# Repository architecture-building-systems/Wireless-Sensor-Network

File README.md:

# Wireless Sensor Network

## Introduction
This repository contains all files needed to reproduce the Wireless Sensor Network (WSN) used for the Data-Driven Building Retrofit Research of the [A/S Chair](http://www.systems.arch.ethz.ch/). 
The WSN is intended to be deployed in residential buildings to collect sensor data for building model calibration. The microcontroller boards are based on the Arduino framework. For wireless communication, XBee radio modules are used.

See the [Wiki](https://github.com/architecture-building-systems/Wireless-Sensor-Network/wiki) for documentation, instructions, and other resources.

## Structure of the WSN
  
Sensor-Kit: (from left to right) two sensor nodes, gateway and router node

The WSN has a modular structure. The main components are the following:
* Gateway
* Router Node
* Sensor Node

On the sensor node, the sensor readings are performed and the data is relayed over router nodes to the gateway using the XBee network. The gateway forwards the data over cellular network to a web server, where the data is stored in a MySQL database. It is also possible to use a sensor node as data logger without any radio communication.

### Sensor Node
Sensor nodes consist of two parts: the main module and the sensor module. The sensor module interfaces the actual sensor(s). It reads out the sensor reading and transmits the result via the serial bus in a unified format to the main module. The main module interfaces the sensor module, radio transceiver, and the battery. It forwards the readings from the sensor module to the gateway. Both, the main module and the sensor module, can be programmed using the Arduino IDE.

#### Main Module
The main module is the same on all sensor nodes. It entails the following:
* Microcontroller (ATmega328p)
* Real-time clock (DS3231)
* Battery (2000mAh LiPo)
* SD-card socket
* XBee radio module (XB24CZ7WIT-004)
* Slide switch and LEDs for debugging
* Power jack for external power
* Connectors to sensor module

The tasks of the main module are:
* Scheduling (RTC or interrupt from sensor module)
* Interfacing the sensor module
* Interfacing XBee
* Interfacing SD-card
* Reading the charge state of the battery
* Switching between normal operation and debugging mode

#### Sensor Module
The sensor module interfaces the actual sensor(s). Each sensor or sensor configuration needs its own sensor module design.
The following sensor modules are available:
* Temperature and Humidity (SHT31)
* Luminosity (TSL2561)
* Pulse
* CO2 (S8)
* Heat Flux (gSKIN XO)
* Dual Temperature (DS18B20)
* Prototyping

There are two kinds of sensor modules: sensor modules for periodic measurements (fixed time interval) and sensor modules for event based measurements (interrupt driven). On the first power-up of the main module, the type of the sensor module is requested, in order to set the mode to periodic measurements or event based measurements. For periodic measurements, the main module is woken up by the RTC on the main module. It then turns on the power to the sensor module. After power-up of the sensor module, it reads out the sensor(s) and transmits the readings over the serial bus. Then the power to the sensor module is cut by the main module and the data is written to the SD-card and/or sent to the gateway via radio.
For event based measurements the sensor module is always powered on. The main module is woken up by an interrupt signal from the sensor module instead of the RTC. The data transfer is the same as for the periodic measurements. 

### Gateway
The gateway receives the data from the sensor nodes and relays the data to a web server via 3G cellular network. The gateway consists of Adafruit Feather 32u4 FONA and a XBee radio-module. The Adafruit Feather 32u4 FONA can be programmed using the Arduino framework. The gateway is powered via USB power supply and needs to be always powered on.

### Router Node
A router node consists of XBee-radio module and SparkFun XBee Explorer Regulated Board. The router node is powered by a wall adapter power supply. It always needs to be powered on.

## Publications
 * [Wireless sensor network for estimating building performance](https://sciencedirect.com/science/article/pii/S0926580519307472)
 * [An easily-deployable wireless sensor network for building energy performance assessment](https://www.sciencedirect.com/science/article/pii/S1876610217329077)
 
 ## Cite us

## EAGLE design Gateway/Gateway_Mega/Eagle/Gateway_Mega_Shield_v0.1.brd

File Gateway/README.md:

# Gateway 
 
A gateway includes the following parts: 
* [Adafruit Feather 32u4 FONA](https://learn.adafruit.com/adafruit-feather-32u4-fona)
* Cellular Antenna
* uFL to SMA Adapter cable
* LiPo Battery (1000mAh) 
* XBee Module 
* USB Power Supply
* Custom PCB 
* 3D Printed Housing 

The router nodes receives the messages form the sensor node with the XBee radio module and forwards the messages over 3G to the webserver. This is done by reading the Xbee payload message and calling a PHP script running on the webserver. The XBee payload is sent as an GET parameter in the URL of the PHP script.
The XBee radio module and the Adafruit Feather 32u4 FONA are both plugged in to the custom PCB. The PCB features pin headers for the Feather 32u4 FONA and XBee radio module. Additionally, there are three indicator LEDs on the PCB. 

## XBee Settings for Gateway
In the current setting we are using XBee S2c (XB24CZ7WIT-004). We use the Firmware for the product family XB24C with the Function set ZIGBEE TH Reg. The Firmware version is 405E.
We use the default settings. Excpetions are listed below:

|Parameter | Value 	| Comment |
|----------|--------|-------|
|ID	       | xxx	  | PAN ID, can be set to anything, but all nodes in the same network must have the same PAN ID |
|CE	       | 1	    | Set if this device is a coordinator (1) or not (0) |
|AP	       | 2	    | API mode with escaping |
|SP	       | AF0    | SP and SN together regulate after how long an end device is forgotten. We set it to the maximum time so that when waking up, our sensor modules are still in the network and not forgotten.|
|SN	       |FFFF    |  |	

The configuration profiles are also available as [files](XBee_Profiles/). All XBees corresponding to one coordinator need to be set to the same PAN ID as the coordinator.

## Other Gateway Versions
The gateway based on the Adafruit Feather 32u4 FONA exhibited unreliable behavior in situations with not good enough cell reception. In these situations the Feather 32u4 FONA would continuously reset. This lead to significant data losses in case studies. To address this issue, we looked into other options: Adafruit FONA boards paired with Arduino Mega or Arduino Uno. The larger memory of the Arduino Mega allows to incorporate a SD card and a real time clock for offline data storage.

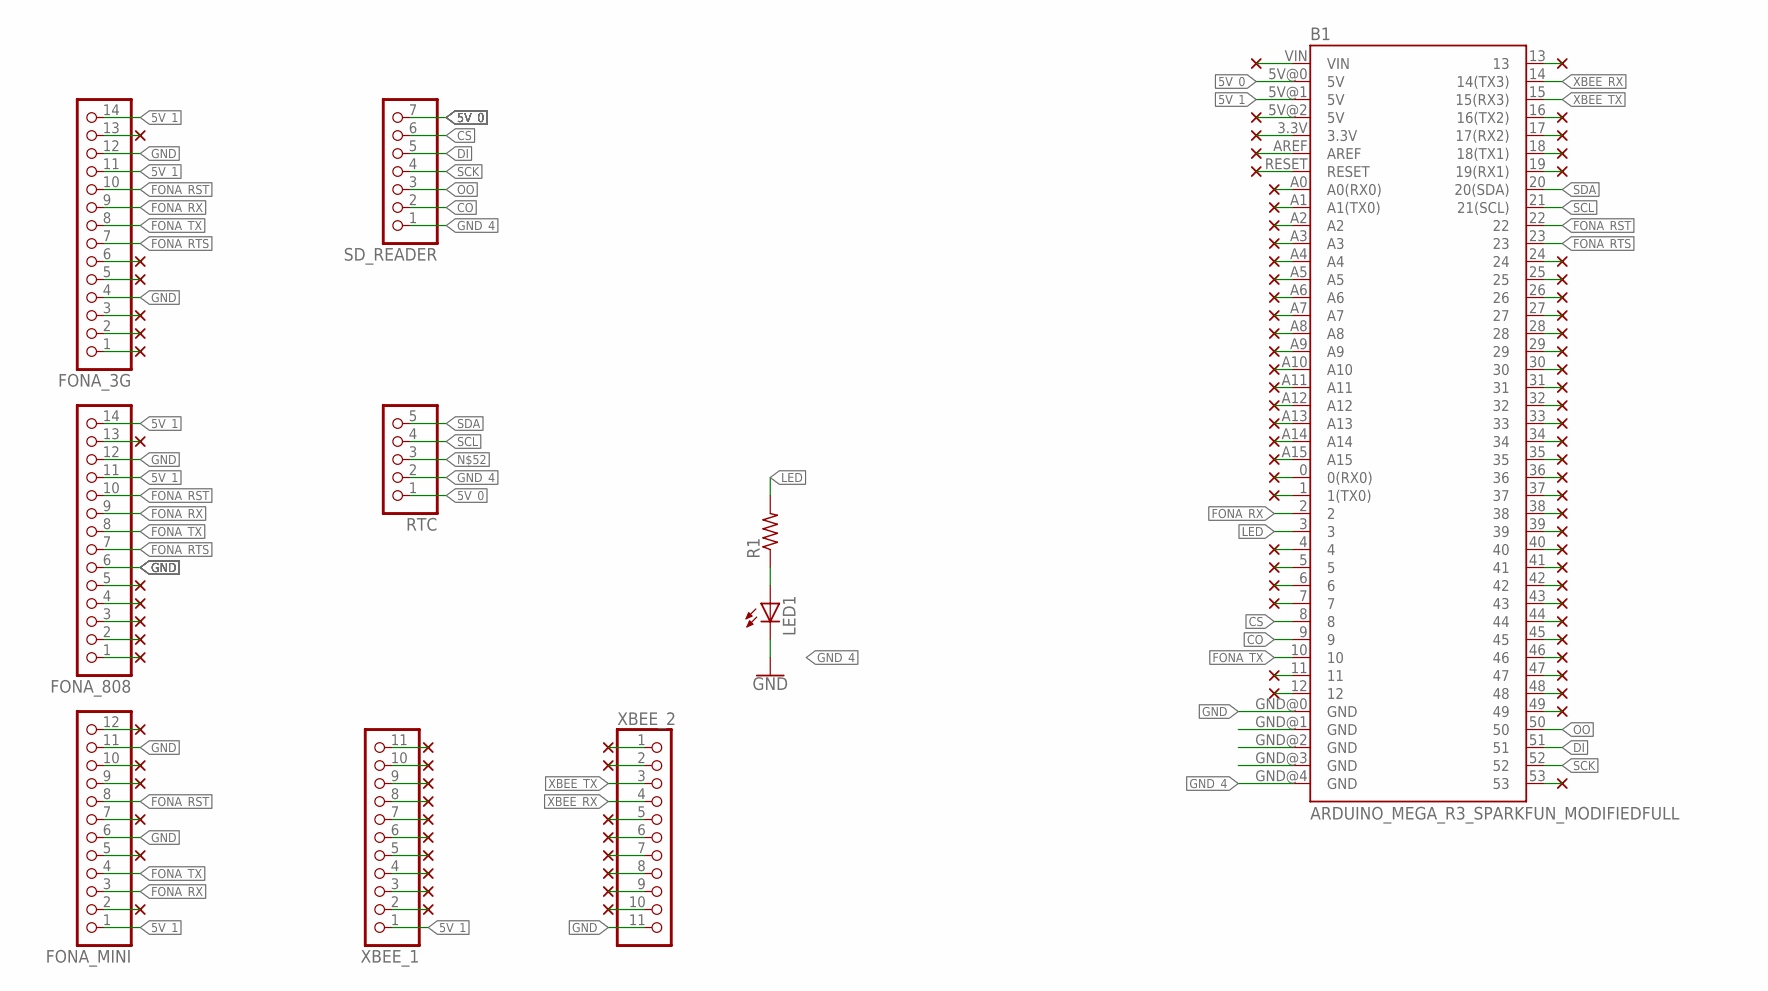
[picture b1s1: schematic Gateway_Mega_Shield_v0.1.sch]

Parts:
B1: ARDUINO_MEGA_R3_SPARKFUN_MODIFIEDFULL; ARDUINO_MEGA_SPARKFUN_MODIFIED
FONA_3G, FONA_808: PINHD-1X14; 1X14
FONA_MINI: PINHD-1X12; 1X12
LED1: LED5MM
R1: R-US_0207/10; 0207/10
RTC: PINHD-1X5; 1X05
SD_READER: PINHD-1X7; 1X07
XBEE_1, XBEE_2: PINHD-1X11; 1X11

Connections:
5V_0: B1.5V@0 (5V), RTC.1, SD_READER.7
5V_1: B1.5V@1 (5V), FONA_3G.11, FONA_3G.14, FONA_808.11, FONA_808.14, FONA_MINI.1, XBEE_1.1
CO: B1.9, SD_READER.2
CS: B1.8, SD_READER.6
DI: B1.51, SD_READER.5
FONA_RST: B1.22, FONA_3G.10, FONA_808.10, FONA_MINI.8
FONA_RTS: B1.23, FONA_3G.7, FONA_808.7
FONA_RX: B1.2, FONA_3G.9, FONA_808.9, FONA_MINI.3
FONA_TX: B1.10, FONA_3G.8, FONA_808.8, FONA_MINI.4
GND: B1.GND@0 (GND), FONA_3G.4, FONA_3G.12, FONA_808.6, FONA_808.12, FONA_MINI.6, FONA_MINI.11, XBEE_2.11
GND_4: B1.GND@4 (GND), LED1.K (C), RTC.2, SD_READER.1
LED: B1.3, R1.2
unnamed: LED1.A, R1.1
OO: B1.50, SD_READER.3
SCK: B1.52, SD_READER.4
SCL: B1.21 (21(SCL)), RTC.4
SDA: B1.20 (20(SDA)), RTC.5
XBEE_RX: B1.14 (14(TX3)), XBEE_2.4
XBEE_TX: B1.15 (15(RX3)), XBEE_2.3

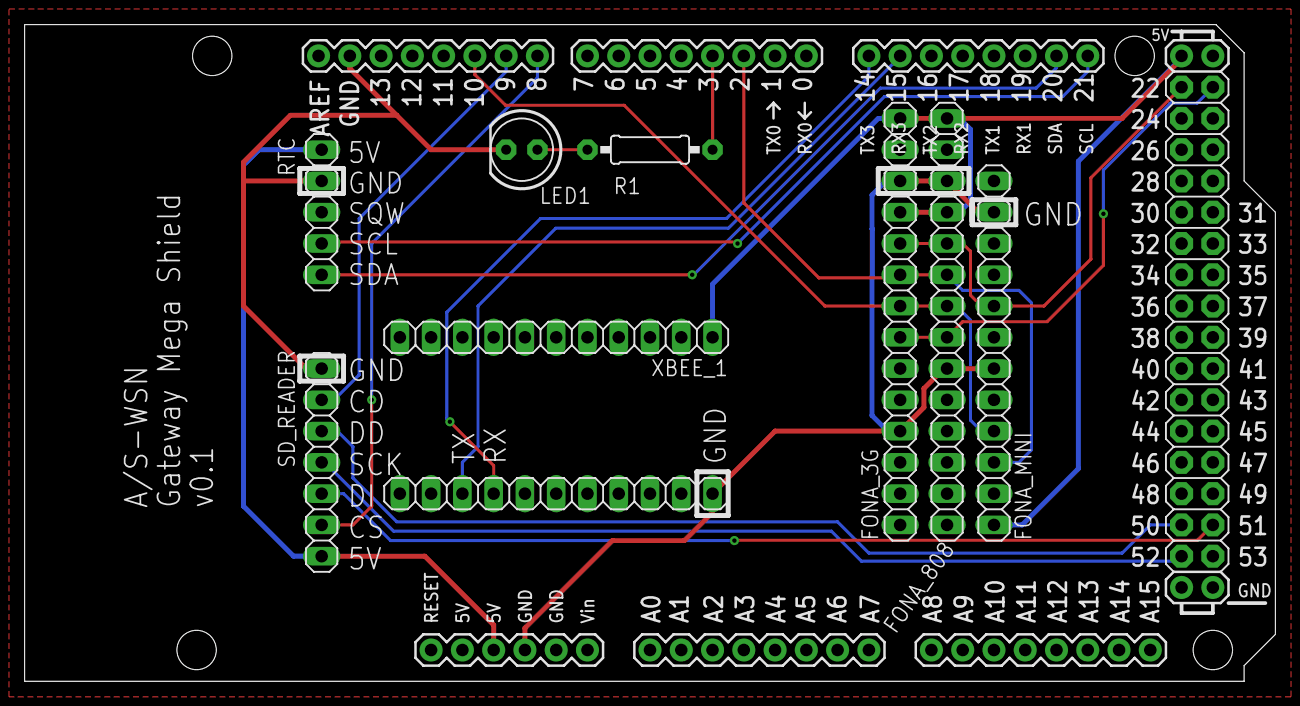
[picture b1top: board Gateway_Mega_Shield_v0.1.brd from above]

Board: 2 copper layers, 101.6 x 53.3 mm, 10 parts (0 on the bottom side), 19 nets.

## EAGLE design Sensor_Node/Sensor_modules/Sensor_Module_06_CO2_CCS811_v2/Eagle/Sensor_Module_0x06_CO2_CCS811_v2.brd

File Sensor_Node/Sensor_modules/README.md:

# Sensor Modules

We are currently revising all sensor modules.

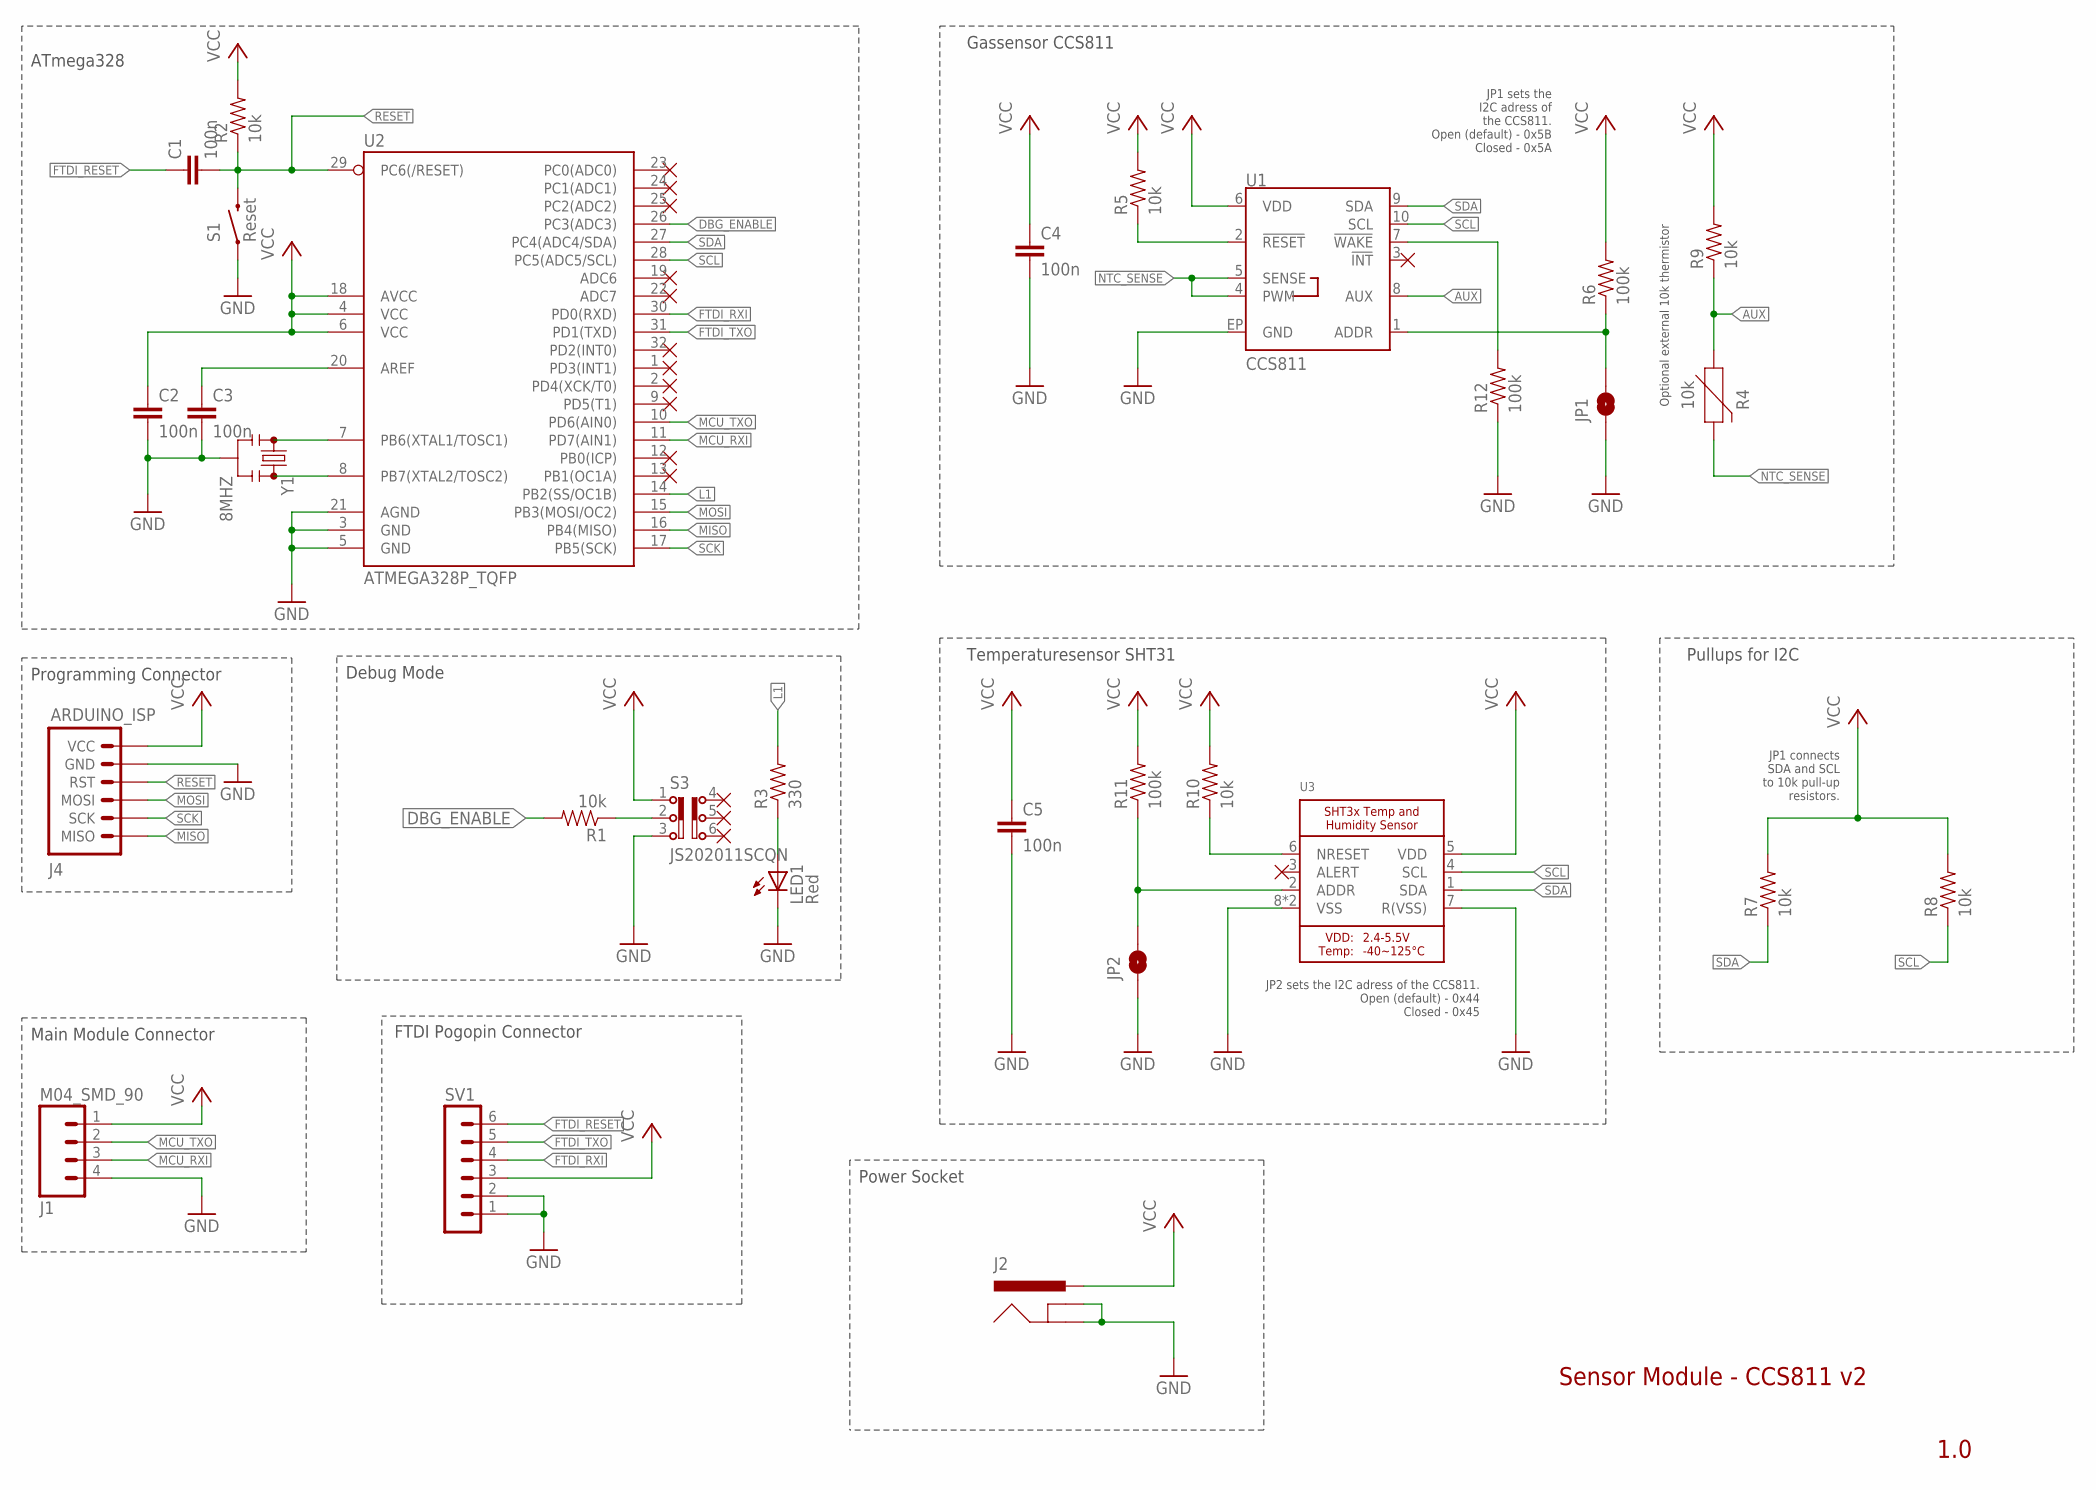
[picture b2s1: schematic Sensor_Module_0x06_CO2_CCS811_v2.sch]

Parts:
C1, C2, C3, C4, C5: 100n; C0805
J1: M04_SMD_90
J2: 5.5x2.1mm Barrel; POWER_JACK_SMD
J4: ARDUINO_ISP; M-2X3
JP1, JP2: SPARKFUN-JUMPERS_JUMPER-SMT_2_NO_SILK; SPARKFUN-JUMPERS_SMT-JUMPER_2_NO_SILK
LED1: Red; SML0805
R1, R2, R5, R7, R8, R9, R10: 10k; 0805
R3: 330; 0805
R4: 10k; CCS811_BREAKOUT_TEMP_0603
R6, R11, R12: 100k; 0805
S1: Reset; M-PUSHBUTTON-SMD
S3: JS202011SCQN
SV1: MA06-1
U1: CCS811; CCS811_BREAKOUT_TEMP_LGA10
U2: ATMEGA328P_TQFP; TQFP32-08
U3: MICROBUILDER_SHT3X
Y1: 8MHZ; RESONATOR-SMD

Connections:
AUX: R4.1, R9.1, U1.8 (AUX)
DBG_ENABLE: R1.2, U2.26 (PC3(ADC3))
FTDI_RESET: C1.1, SV1.6
FTDI_RXI: SV1.4, U2.30 (PD0(RXD))
FTDI_TXO: SV1.5, U2.31 (PD1(TXD))
GND: C2.2, C3.2, C4.2, C5.2, J1.4, J2.GND (GNDBREAK), J2.P$4 (GND), J4.P$5 (GND), JP1.1, JP2.1, LED1.C, R12.1, S1.1 (LEFT), S1.2 (LEFT), S3.3, SV1.1, SV1.2, U1.EP (GND), U2.3 (GND), U2.5 (GND), U2.21 (AGND), U3.7 (R(VSS)), U3.8 (VSS), U3.THERMAL (VSS), Y1.2
L1: R3.2, U2.14 (PB2(SS/OC1B))
MCU_RXI: J1.3, U2.11 (PD7(AIN1))
MCU_TXO: J1.2, U2.10 (PD6(AIN0))
MISO: J4.P$1 (MISO), U2.16 (PB4(MISO))
MOSI: J4.P$3 (MOSI), U2.15 (PB3(MOSI/OC2))
unnamed: U2.8 (PB7(XTAL2/TOSC2)), Y1.3
unnamed: U2.7 (PB6(XTAL1/TOSC1)), Y1.1
unnamed: R1.1, S3.2
unnamed: JP1.2, R6.1, U1.1 (ADDR)
unnamed: R12.2, U1.7 (!WAKE!)
unnamed: R10.1, U3.6 (NRESET)
unnamed: JP2.2, R11.1, U3.2 (ADDR)
unnamed: C3.1, U2.20 (AREF)
unnamed: LED1.A, R3.1
NTC_SENSE: R4.2, U1.4 (PWM), U1.5 (SENSE)
RESET: C1.2, J4.P$4 (RST), R2.1, S1.3 (RIGHT), S1.4 (RIGHT), U2.29 (PC6(/RESET))
SCK: J4.P$2 (SCK), U2.17 (PB5(SCK))
SCL: R8.1, U1.10 (SCL), U2.28 (PC5(ADC5/SCL)), U3.4 (SCL)
SDA: R7.1, U1.9 (SDA), U2.27 (PC4(ADC4/SDA)), U3.1 (SDA)
SENS_RES: R5.1, U1.2 (!RESET!)
VCC: C2.1, C4.1, C5.1, J1.1, J2.VIN0 (PWR), J2.VIN1 (PWR), J4.P$6 (VCC), R2.2, R5.2, R6.2, R7.2, R8.2, R9.2, R10.2, R11.2, S3.1, SV1.3, U1.6 (VDD), U2.4 (VCC), U2.6 (VCC), U2.18 (AVCC), U3.5 (VDD)

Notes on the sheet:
Debug Mode
Programming Connector
ATmega328
Main Module Connector
Sensor Module - CCS811 v2
1.0
FTDI Pogopin Connector
JP1 sets the I2C adress of the CCS811. Open (default) - 0x5B Closed - 0x5A
JP1 connects SDA and SCL to 10k pull-up resistors.
Optional external 10k thermistor
JP2 sets the I2C adress of the CCS811. Open (default) - 0x44 Closed - 0x45
Gassensor CCS811
Temperaturesensor SHT31
Pullups for I2C
Power Socket

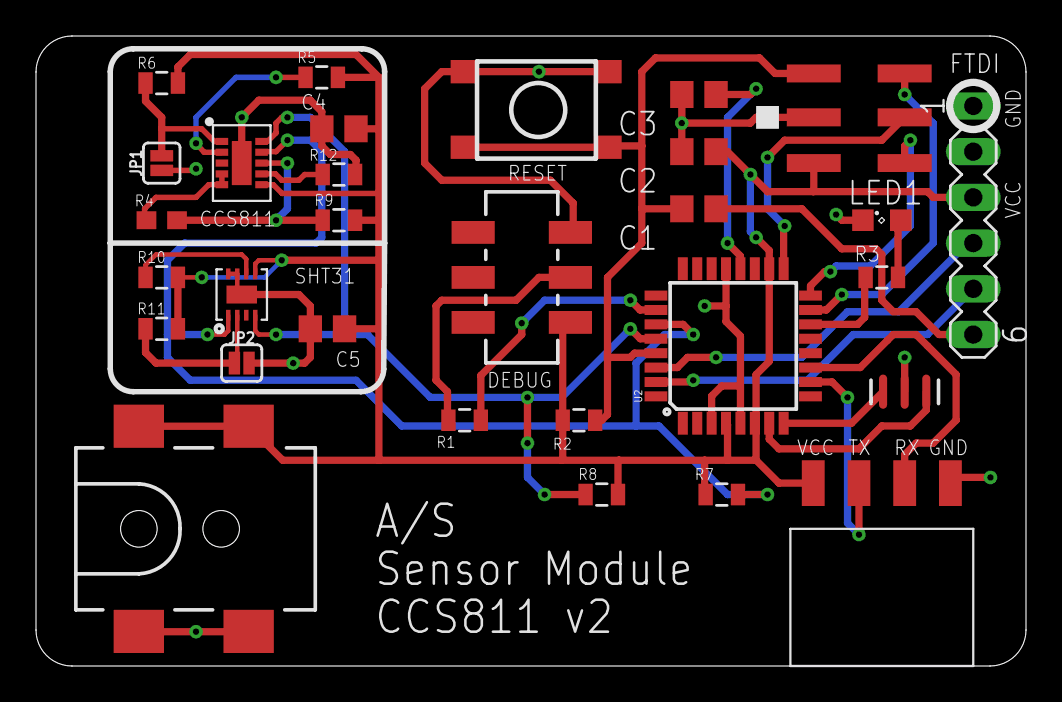
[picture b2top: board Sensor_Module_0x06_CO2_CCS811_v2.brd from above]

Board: 2 copper layers, 55.0 x 35.0 mm, 30 parts (0 on the bottom side), 27 nets.

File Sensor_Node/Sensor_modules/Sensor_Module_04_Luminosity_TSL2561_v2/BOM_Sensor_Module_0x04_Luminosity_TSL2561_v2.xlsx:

BOM_Sensor_Board_0x04_Luminosity_TSL2561_v2
Name | Identifier | Pieces | Price/Piece | Total | Link
ATMEGA328
Microcontroller ATmega328p | U2 | 1 | 2.0699999999999998 | 2.0699999999999998 | https://www.digikey.ch/short/39mzf8
8 MHz Resonator | Y1 | 1 | 0.48 | 0.48 | https://www.digikey.ch/short/39mz18
Reset-Button | S1 | 1 | 0.18 | 0.18 | https://www.digikey.ch/short/39mz1b
100nF-Capacitor 0805 | C1, C2, C3 | 3 | 0.1 | 0.30000000000000004 | https://www.digikey.ch/short/39mzwv
10k-Resistor 0805 | R2 | 1 | 0.1 | 0.1 | https://www.digikey.ch/short/jmv2r2
Luminosity-Sensor TSL2561
TSL2561 | U1 | 1 | 4.16 | 4.16 | https://www.digikey.ch/product-detail/de/ams/TSL2561T/TSL256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
100nF-Capacitor 0805 | C4 | 1 | 0.1 | 0.1 | https://www.digikey.ch/short/39mzwv
10k-Resistor 0805 | R4, R5 | 2 | 0.1 | 0.2 | https://www.digikey.ch/short/jmv2r2
Communication Module connector
AMP 4pin connector | J1 | 1 | 0.7 | 0.7 | https://www.digikey.ch/product-detail/en/te-connectivity-amp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
Programming Connector
SPI Pin Header | J4 | 1 | 0.43 | 0.43 | https://www.digikey.ch/short/39mz0t
Debug Mode
LED rot | LED | 1 | 0.38 | 0.38 | https://www.digikey.ch/product-detail/de/lite-on-inc/LTST-C1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
10k-Resistor 0805 | R1 | 1 | 0.1 | 0.1 | https://www.digikey.ch/short/jmv2r2
330-Resistor 0805 | R3 | 1 | 0.1 | 0.1 | https://www.digikey.ch/short/39m470
Debug Switch | S3 | 1 | 0.48 | 0.48 | https://www.digikey.ch/short/39mzvc
Total price: | 9.7799999999999994

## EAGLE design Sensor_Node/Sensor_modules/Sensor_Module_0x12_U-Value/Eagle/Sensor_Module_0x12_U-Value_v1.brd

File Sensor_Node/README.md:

# Sensor Node
 
Sensor node integrate sensors, power management and wireless communication. The sensor nodes itself is modular and consists of one main module (MM) and one sensor module (SM). The two PCBs and the battery are protected by a 3D printed housing, consisting of two parts that latch together.
The two components can be exchanged independently and are connected by power bus and a serial communication bus. 
The sensor module has a microcontroller, which interfaces the onboard sensors. The sensor data is transferred in a standardized format via the serial communication bus to the main module. The main module receives the readings form the sensor board, saves them with a timestamp from the real time clock (RTC) to the SD-card and sends the data via ZigBee to the gateway.

## XBee Settings for Sensor Nodes (/Main Modules)
In the current setting we are using XBee S2c (XB24CZ7WIT-004). We use the firmware for the product family XB24C with the function set ZIGBEE TH Reg. The firmware version is 405E.
We use the default settings. Excpetions are listed below:

|Parameter | Value	| Comment |
|----------|--------|-------|
|ID	       | xxx	  | PAN ID, can be set to anything, but all nodes in the same network must have the same PAN ID |
|AP	       | 2	    | API mode with escaping |
|SM        | 1      | Allows sleep mode to be controlled through sleep pin|

The configuration profiles are also available as [files](XBee_Profiles/). All XBees corresponding to one coordinator need to be set to the same PAN ID as the coordinator.

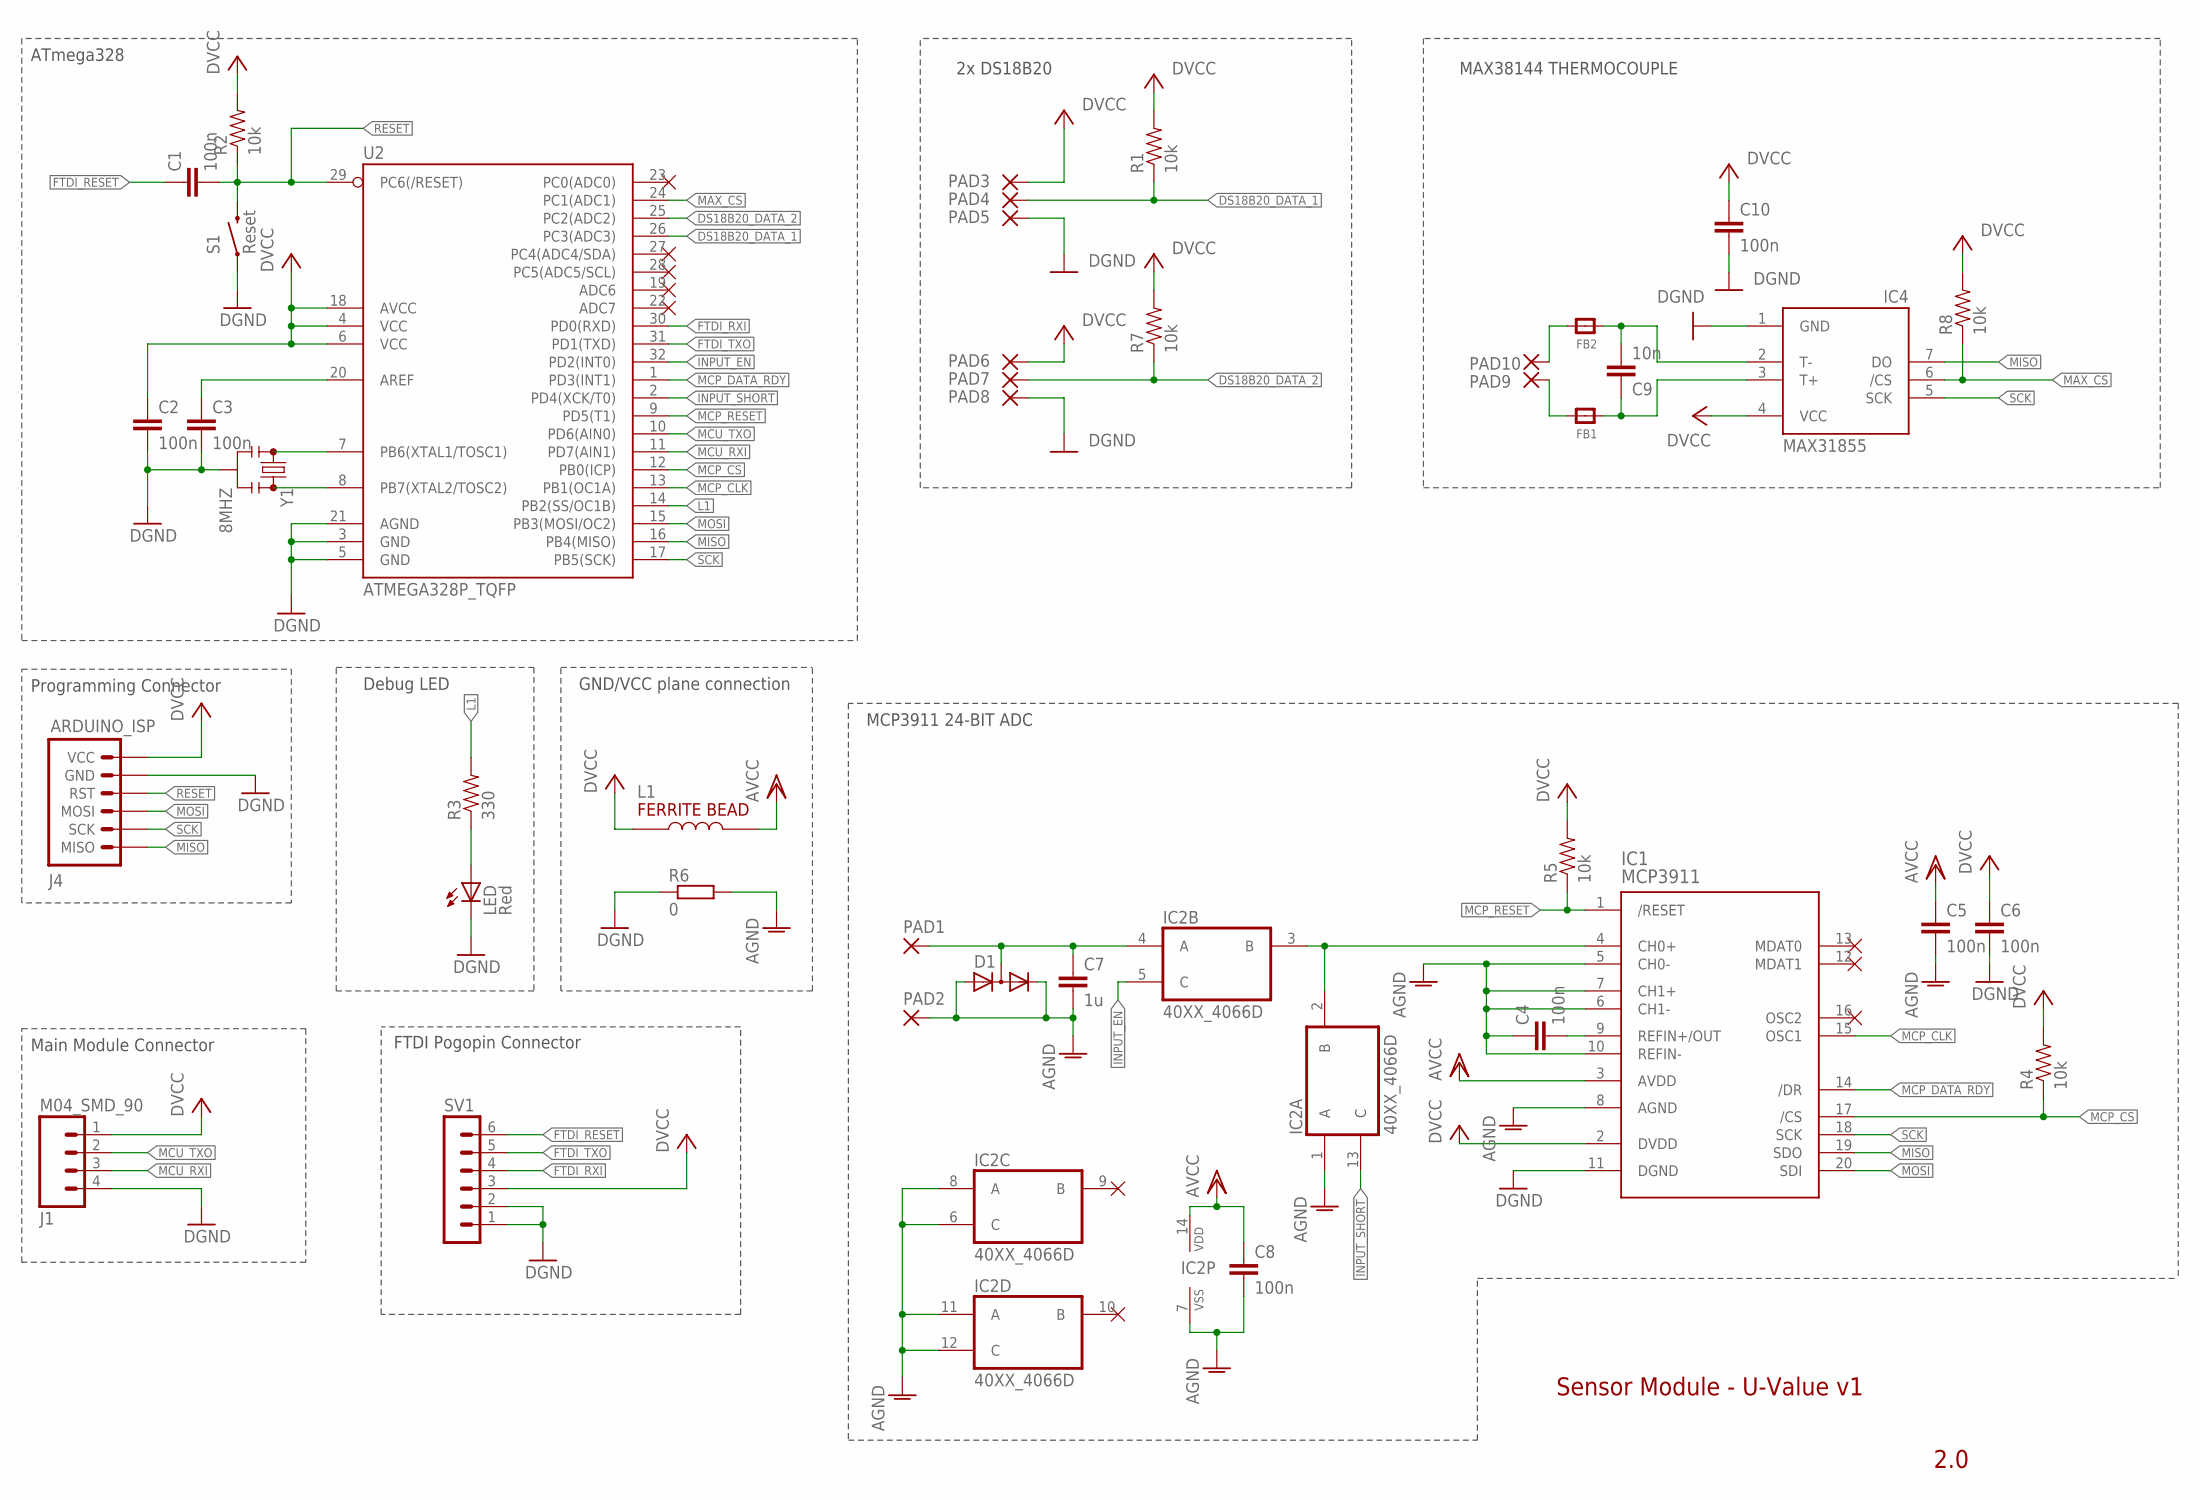
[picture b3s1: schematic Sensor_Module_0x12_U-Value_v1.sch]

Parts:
C1, C2, C3, C4, C5, C6, C8, C10: 100n; C0805
C7: 1u; C0805
C9: 10n; C0805
D1: LEDXLAMP_BAV99; LEDXLAMP_SOT23
FB1, FB2: MICROBUILDER_FERRITE_0805MP; MICROBUILDER__0805MP
IC1: MCP3911; HEATFLOW_SSOP20
IC2: 40XX_4066D; 40XX_SO14
IC4: MAX31855; ADAFRUIT_SO08
J1: M04_SMD_90
J4: ARDUINO_ISP; M-2X3
L1: HEATFLOW2_74279220601; HEATFLOW2_0805
LED: Red; SML0805
PAD1, PAD2, PAD3, PAD4, PAD5, PAD6, PAD7, PAD8, PAD9, PAD10: WIREPADSMD1,27-254; SMD1,27-2,54
R1, R2, R4, R5, R7, R8: 10k; 0805
R3: 330; 0805
R6: 0; RESISTOR_M0805
S1: Reset; M-PUSHBUTTON-SMD
SV1: MA06-1
U2: ATMEGA328P_TQFP; TQFP32-08
Y1: 8MHZ; RESONATOR-SMD

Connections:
AGND: C4.1, C5.2, C7.2, C8.2, D1.1 (A), D1.2 (C), IC1.5 (CH0-), IC1.6 (CH1-), IC1.7 (CH1+), IC1.8 (AGND), IC1.10 (REFIN-), IC2.1 (A), IC2.6 (C), IC2.7 (VSS), IC2.8 (A), IC2.11 (A), IC2.12 (C), PAD2.1, R6.2
AVCC: C5.1, C8.1, IC1.3 (AVDD), IC2.14 (VDD), L1.2
DGND: C2.2, C3.2, C6.2, C10.2, IC1.11 (DGND), IC4.1 (GND), J1.4, J4.P$5 (GND), LED.C, PAD5.1, PAD8.1, R6.1, S1.1 (LEFT), S1.2 (LEFT), SV1.1, SV1.2, U2.3 (GND), U2.5 (GND), U2.21 (AGND), Y1.2
DS18B20_DATA_1: PAD4.1, R1.1, U2.26 (PC3(ADC3))
DS18B20_DATA_2: PAD7.1, R7.1, U2.25 (PC2(ADC2))
DVCC: C2.1, C6.1, C10.1, IC1.2 (DVDD), IC4.4 (VCC), J1.1, J4.P$6 (VCC), L1.1, PAD3.1, PAD6.1, R1.2, R2.2, R4.2, R5.2, R7.2, R8.2, SV1.3, U2.4 (VCC), U2.6 (VCC), U2.18 (AVCC)
FTDI_RESET: C1.1, SV1.6
FTDI_RXI: SV1.4, U2.30 (PD0(RXD))
FTDI_TXO: SV1.5, U2.31 (PD1(TXD))
INPUT_EN: IC2.5 (C), U2.32 (PD2(INT0))
INPUT_SHORT: IC2.13 (C), U2.2 (PD4(XCK/T0))
L1: R3.2, U2.14 (PB2(SS/OC1B))
MAX_CS: IC4.6 (/CS), R8.1, U2.24 (PC1(ADC1))
MCP_CLK: IC1.15 (OSC1), U2.13 (PB1(OC1A))
MCP_CS: IC1.17 (/CS), R4.1, U2.12 (PB0(ICP))
MCP_DATA_RDY: IC1.14 (/DR), U2.1 (PD3(INT1))
MCP_RESET: IC1.1 (/RESET), R5.1, U2.9 (PD5(T1))
MCU_RXI: J1.3, U2.11 (PD7(AIN1))
MCU_TXO: J1.2, U2.10 (PD6(AIN0))
MISO: IC1.19 (SDO), IC4.7 (DO), J4.P$1 (MISO), U2.16 (PB4(MISO))
MOSI: IC1.20 (SDI), J4.P$3 (MOSI), U2.15 (PB3(MOSI/OC2))
unnamed: U2.8 (PB7(XTAL2/TOSC2)), Y1.3
unnamed: U2.7 (PB6(XTAL1/TOSC1)), Y1.1
unnamed: FB1.1, PAD9.1
unnamed: C4.2, IC1.9 (REFIN+/OUT)
unnamed: IC1.4 (CH0+), IC2.2 (B), IC2.3 (B)
unnamed: C7.1, D1.3 (AC), IC2.4 (A), PAD1.1
unnamed: FB2.1, PAD10.1
unnamed: C9.2, FB2.2, IC4.2 (T-)
unnamed: C9.1, FB1.2, IC4.3 (T+)
unnamed: C3.1, U2.20 (AREF)
unnamed: LED.A, R3.1
RESET: C1.2, J4.P$4 (RST), R2.1, S1.3 (RIGHT), S1.4 (RIGHT), U2.29 (PC6(/RESET))
SCK: IC1.18 (SCK), IC4.5 (SCK), J4.P$2 (SCK), U2.17 (PB5(SCK))

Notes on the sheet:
Debug LED
Programming Connector
ATmega328
Main Module Connector
Sensor Module - U-Value v1
2.0
FTDI Pogopin Connector
2x DS18B20
MAX38144 THERMOCOUPLE
GND/VCC plane connection
MCP3911 24-BIT ADC

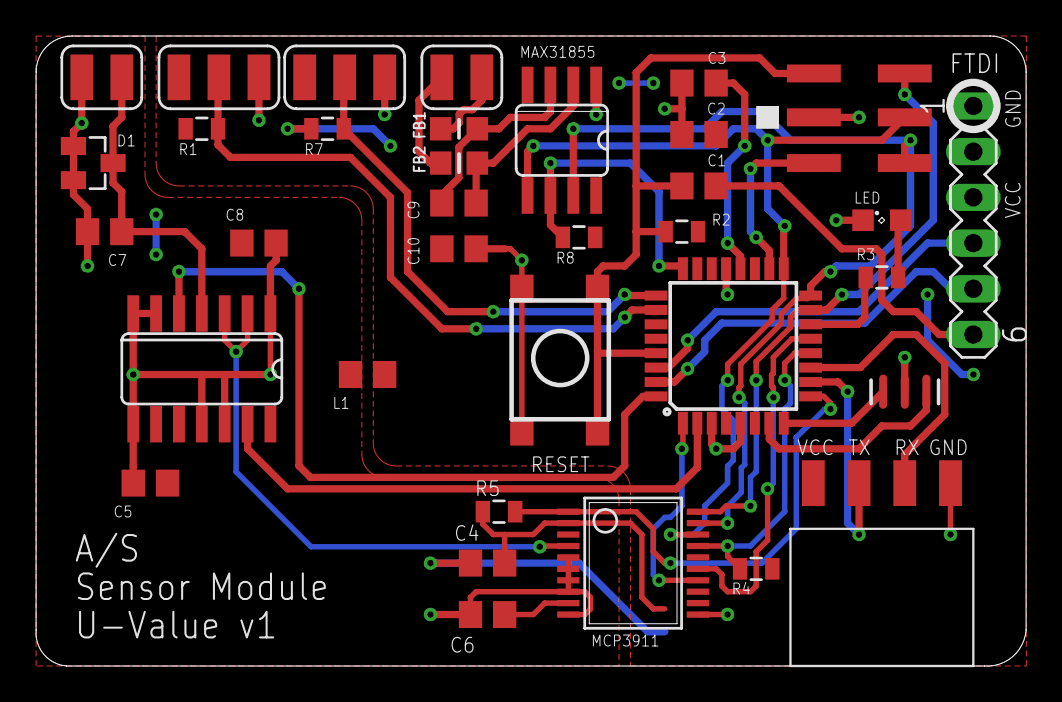
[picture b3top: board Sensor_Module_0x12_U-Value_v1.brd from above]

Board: 2 copper layers, 55.0 x 35.0 mm, 42 parts (1 on the bottom side), 34 nets.

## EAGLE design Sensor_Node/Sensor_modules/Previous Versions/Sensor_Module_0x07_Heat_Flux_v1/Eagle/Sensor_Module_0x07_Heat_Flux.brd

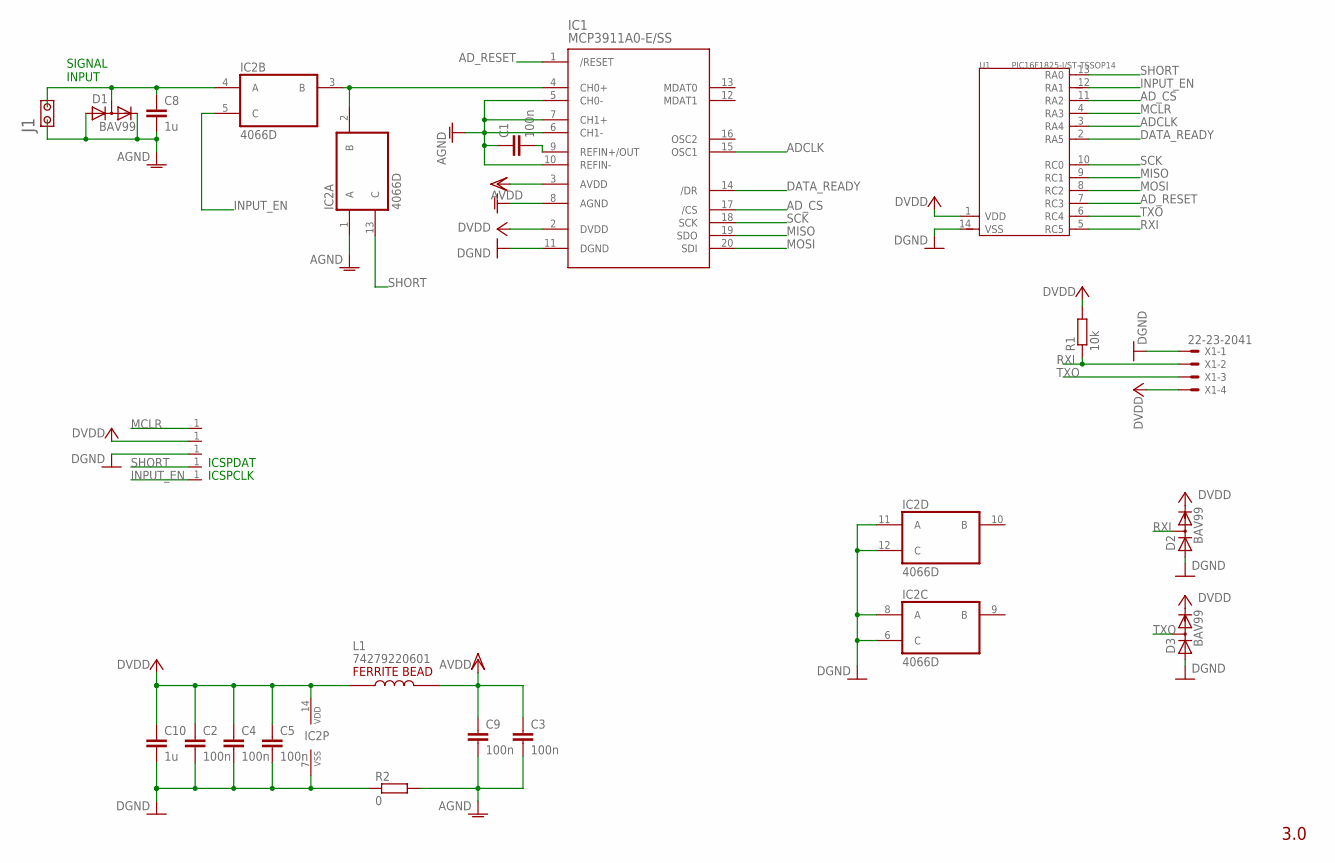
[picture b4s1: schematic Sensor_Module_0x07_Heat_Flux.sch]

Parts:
C1, C2, C3, C4, C5, C9: 100n; C0805
C8, C10: 1u; C0805
D1, D2, D3: BAV99; SOT23
IC1: MCP3911A0-E/SS; SSOP20
IC2: 4066D; SO14
J1: CON2X1
L1: 74279220601; 0805
PIN1, PIN2, PIN3, PIN4, PIN5: CON1X1
R1: 10k; M0805
R2: 0; M0805
U1: PIC16F1825-I/ST-TSSOP14; TSSOP14-0.65-5X4.4MM
X1: 22-23-2041

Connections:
ADCLK: IC1.15 (OSC1), U1.3 (RA4)
AD_CS: IC1.17 (/CS), U1.11 (RA2)
AD_RESET: IC1.1 (/RESET), U1.7 (RC3)
AGND: C1.1, C3.2, C8.2, C9.2, D1.1 (A), D1.2 (C), IC1.5 (CH0-), IC1.6 (CH1-), IC1.7 (CH1+), IC1.8 (AGND), IC1.10 (REFIN-), IC2.1 (A), J1.1, R2.2
AVDD: C3.1, C9.1, IC1.3 (AVDD), L1.2
DATA_READY: IC1.14 (/DR), U1.2 (RA5)
DGND: C2.2, C4.2, C5.2, C10.2, D2.1 (A), D3.1 (A), IC1.11 (DGND), IC2.6 (C), IC2.7 (VSS), IC2.8 (A), IC2.11 (A), IC2.12 (C), PIN3.1, R2.1, U1.14 (VSS), X1.1
DVDD: C2.1, C4.1, C5.1, C10.1, D2.2 (C), D3.2 (C), IC1.2 (DVDD), IC2.14 (VDD), L1.1, PIN2.1, R1.2, U1.1 (VDD), X1.4
INPUT_EN: IC2.5 (C), PIN5.1, U1.12 (RA1)
MCLR: PIN1.1, U1.4 (RA3)
MISO: IC1.19 (SDO), U1.9 (RC1)
MOSI: IC1.20 (SDI), U1.8 (RC2)
unnamed: C1.2, IC1.9 (REFIN+/OUT)
unnamed: IC1.4 (CH0+), IC2.2 (B), IC2.3 (B)
unnamed: C8.1, D1.3 (AC), IC2.4 (A), J1.2
RXI: D2.3 (AC), R1.1, U1.5 (RC5), X1.2
SCK: IC1.18 (SCK), U1.10 (RC0)
SHORT: IC2.13 (C), PIN4.1, U1.13 (RA0)
TXO: D3.3 (AC), U1.6 (RC4), X1.3

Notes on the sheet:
SIGNAL INPUT
ICSPCLK
ICSPDAT
3.0

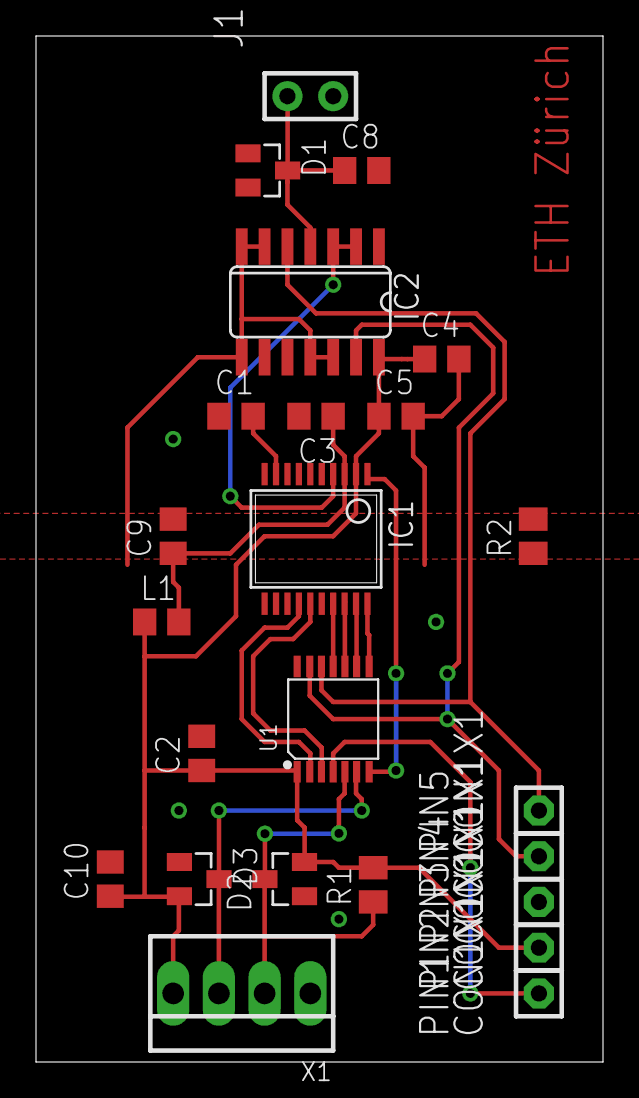
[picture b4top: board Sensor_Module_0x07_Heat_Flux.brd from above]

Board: 2 copper layers, 31.5 x 57.0 mm, 24 parts (0 on the bottom side), 19 nets.

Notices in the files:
parts and their libraries:
SparkFun-Boards: Licensing: Creative Commons ShareAlike 4.0 International - https://creativecommons.org/licenses/by-sa/4.0
